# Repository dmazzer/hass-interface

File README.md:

# hass-interface
Hardware interface for Home Assistant

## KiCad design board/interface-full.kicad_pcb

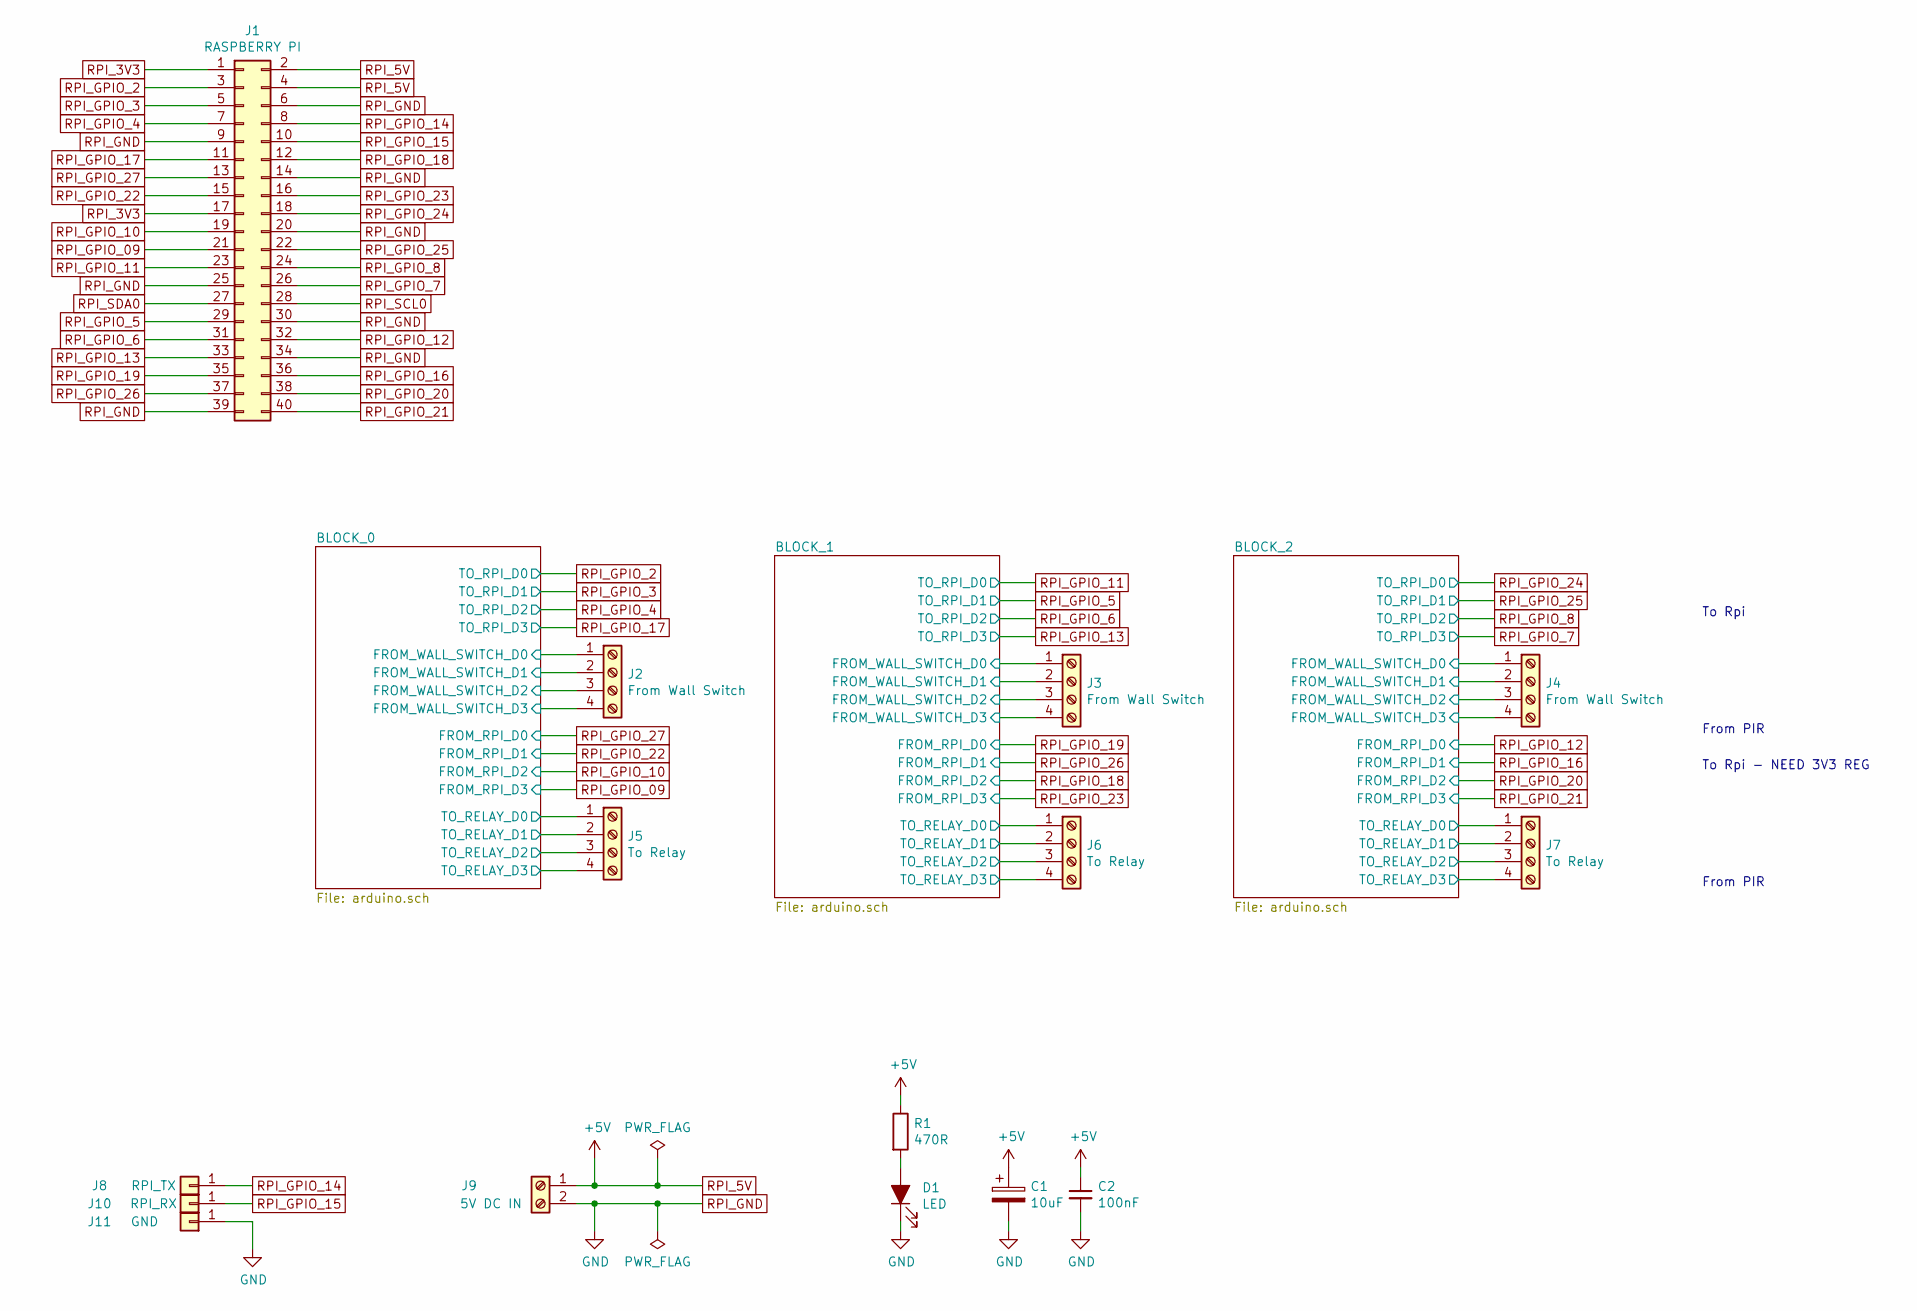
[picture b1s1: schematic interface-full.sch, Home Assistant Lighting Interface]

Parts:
C1: 10uF; CP_Radial_D5.0mm_P2.50mm
C2: 100nF; C_0805_2012Metric_Pad1.15x1.40mm_HandSolder
D1: LED; LED_1206_3216Metric_Pad1.42x1.75mm_HandSolder
J1: RASPBERRY PI; PinSocket_2x20_P2.54mm_Vertical
J2, J3, J4: From Wall Switch; TerminalBlock_Phoenix_MKDS-1,5-4-5.08_1x04_P5.08mm_Horizont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
J5, J6, J7: To Relay; TerminalBlock_Phoenix_MKDS-1,5-4-5.08_1x04_P5.08mm_Horizont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
J8: RPI_TX; PinHeader_1x01_P2.54mm_Vertical
J9: 5V DC IN; TerminalBlock_Phoenix_MKDS-1,5-2-5.08_1x02_P5.08mm_Horizont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
J10: RPI_RX; PinHeader_1x01_P2.54mm_Vertical
J11: GND; PinHeader_1x01_P2.54mm_Vertical
R1: 470R; R_0805_2012Metric_Pad1.15x1.40mm_HandSolder

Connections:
/BLOCK_0/FROM_WALL_SWITCH_D0: J2.1; also elsewhere on the board
/BLOCK_0/FROM_WALL_SWITCH_D1: J2.2; also elsewhere on the board
/BLOCK_0/FROM_WALL_SWITCH_D2: J2.3; also elsewhere on the board
/BLOCK_0/FROM_WALL_SWITCH_D3: J2.4; also elsewhere on the board
/BLOCK_0/TO_RELAY_D0: J5.1; also elsewhere on the board
/BLOCK_0/TO_RELAY_D1: J5.2; also elsewhere on the board
/BLOCK_0/TO_RELAY_D2: J5.3; also elsewhere on the board
/BLOCK_0/TO_RELAY_D3: J5.4; also elsewhere on the board
/BLOCK_1/FROM_WALL_SWITCH_D0: J3.1; also elsewhere on the board
/BLOCK_1/FROM_WALL_SWITCH_D1: J3.2; also elsewhere on the board
/BLOCK_1/FROM_WALL_SWITCH_D2: J3.3; also elsewhere on the board
/BLOCK_1/FROM_WALL_SWITCH_D3: J3.4; also elsewhere on the board
/BLOCK_1/TO_RELAY_D0: J6.1; also elsewhere on the board
/BLOCK_1/TO_RELAY_D1: J6.2; also elsewhere on the board
/BLOCK_1/TO_RELAY_D2: J6.3; also elsewhere on the board
/BLOCK_1/TO_RELAY_D3: J6.4; also elsewhere on the board
/BLOCK_2/FROM_WALL_SWITCH_D0: J4.1; also elsewhere on the board
/BLOCK_2/FROM_WALL_SWITCH_D1: J4.2; also elsewhere on the board
/BLOCK_2/FROM_WALL_SWITCH_D2: J4.3; also elsewhere on the board
/BLOCK_2/FROM_WALL_SWITCH_D3: J4.4; also elsewhere on the board
/BLOCK_2/TO_RELAY_D0: J7.1; also elsewhere on the board
/BLOCK_2/TO_RELAY_D1: J7.2; also elsewhere on the board
/BLOCK_2/TO_RELAY_D2: J7.3; also elsewhere on the board
/BLOCK_2/TO_RELAY_D3: J7.4; also elsewhere on the board
unnamed: D1.2 (A), R1.2
RPI_3V3: J1.1, J1.17
RPI_5V: C1.1, C2.1, J1.2, J1.4, J9.1, R1.1; also elsewhere on the board
RPI_GND: C1.2, C2.2, D1.1 (K), J1.6, J1.9, J1.14, J1.20, J1.25, J1.30, J1.34, J1.39, J9.2, J11.1; also elsewhere on the board
RPI_GPIO_2: J1.3; also elsewhere on the board
RPI_GPIO_3: J1.5; also elsewhere on the board
RPI_GPIO_4: J1.7; also elsewhere on the board
RPI_GPIO_5: J1.29; also elsewhere on the board
RPI_GPIO_6: J1.31; also elsewhere on the board
RPI_GPIO_7: J1.26; also elsewhere on the board
RPI_GPIO_8: J1.24; also elsewhere on the board
RPI_GPIO_09: J1.21; also elsewhere on the board
RPI_GPIO_10: J1.19; also elsewhere on the board
RPI_GPIO_11: J1.23; also elsewhere on the board
RPI_GPIO_12: J1.32; also elsewhere on the board
RPI_GPIO_13: J1.33; also elsewhere on the board
RPI_GPIO_14: J1.8, J8.1
RPI_GPIO_15: J1.10, J10.1
RPI_GPIO_16: J1.36; also elsewhere on the board
RPI_GPIO_17: J1.11; also elsewhere on the board
RPI_GPIO_18: J1.12; also elsewhere on the board
RPI_GPIO_19: J1.35; also elsewhere on the board
RPI_GPIO_20: J1.38; also elsewhere on the board
RPI_GPIO_21: J1.40; also elsewhere on the board
RPI_GPIO_22: J1.15; also elsewhere on the board
RPI_GPIO_23: J1.16; also elsewhere on the board
RPI_GPIO_24: J1.18; also elsewhere on the board
RPI_GPIO_25: J1.22; also elsewhere on the board
RPI_GPIO_26: J1.37; also elsewhere on the board
RPI_GPIO_27: J1.13; also elsewhere on the board
RPI_SCL0: J1.28
RPI_SDA0: J1.27

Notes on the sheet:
From PIR
To Rpi
To Rpi - NEED 3V3 REG

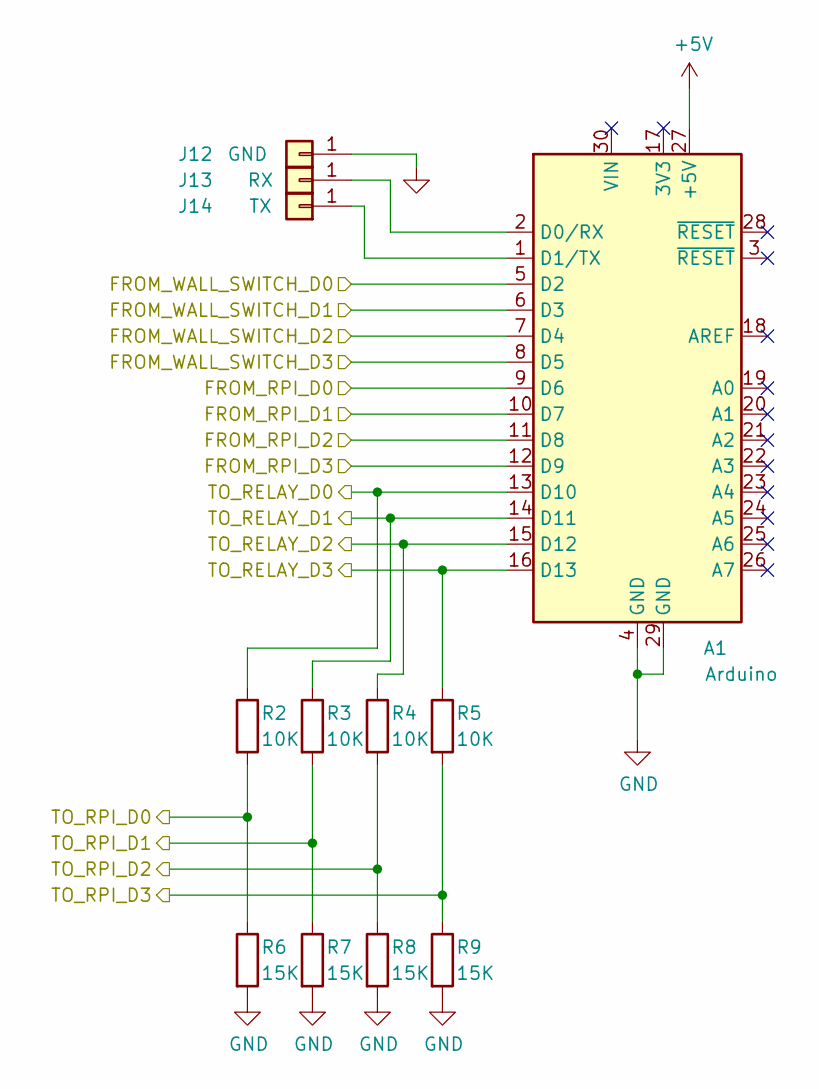
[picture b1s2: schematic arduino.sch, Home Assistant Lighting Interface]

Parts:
A1: Arduino; Arduino_Nano
J12: GND; PinHeader_1x01_P2.54mm_Vertical
J13: RX; PinHeader_1x01_P2.54mm_Vertical
J14: TX; PinHeader_1x01_P2.54mm_Vertical
R2, R3, R4, R5: 10K; R_0805_2012Metric_Pad1.15x1.40mm_HandSolder
R6, R7, R8, R9: 15K; R_0805_2012Metric_Pad1.15x1.40mm_HandSolder

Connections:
/BLOCK_0/FROM_WALL_SWITCH_D0: A1.5 (D2); also elsewhere on the board
/BLOCK_0/FROM_WALL_SWITCH_D1: A1.6 (D3); also elsewhere on the board
/BLOCK_0/FROM_WALL_SWITCH_D2: A1.7 (D4); also elsewhere on the board
/BLOCK_0/FROM_WALL_SWITCH_D3: A1.8 (D5); also elsewhere on the board
/BLOCK_0/TO_RELAY_D0: A1.13 (D10), R2.1; also elsewhere on the board
/BLOCK_0/TO_RELAY_D1: A1.14 (D11), R3.1; also elsewhere on the board
/BLOCK_0/TO_RELAY_D2: A1.15 (D12), R4.1; also elsewhere on the board
/BLOCK_0/TO_RELAY_D3: A1.16 (D13), R5.1; also elsewhere on the board
unnamed: A1.1 (D1/TX), J14.1
unnamed: A1.2 (D0/RX), J13.1
RPI_5V: A1.27 (+5V); also elsewhere on the board
RPI_GND: A1.4 (GND), A1.29 (GND), J12.1, R6.2, R7.2, R8.2, R9.2; also elsewhere on the board
RPI_GPIO_2: R2.2, R6.1; also elsewhere on the board
RPI_GPIO_3: R3.2, R7.1; also elsewhere on the board
RPI_GPIO_4: R4.2, R8.1; also elsewhere on the board
RPI_GPIO_09: A1.12 (D9); also elsewhere on the board
RPI_GPIO_10: A1.11 (D8); also elsewhere on the board
RPI_GPIO_17: R5.2, R9.1; also elsewhere on the board
RPI_GPIO_22: A1.10 (D7); also elsewhere on the board
RPI_GPIO_27: A1.9 (D6); also elsewhere on the board

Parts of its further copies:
A2, A3: Arduino; Arduino_Nano
J15, J18: GND; PinHeader_1x01_P2.54mm_Vertical
J16, J19: RX; PinHeader_1x01_P2.54mm_Vertical
J17, J20: TX; PinHeader_1x01_P2.54mm_Vertical
R11, R12, R13, R14, R20, R21, R22, R23: 10K; R_0805_2012Metric_Pad1.15x1.40mm_HandSolder
R15, R16, R17, R18, R24, R25, R26, R27: 15K; R_0805_2012Metric_Pad1.15x1.40mm_HandSolder

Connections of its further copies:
/BLOCK_1/FROM_WALL_SWITCH_D0: A2.5 (D2); also elsewhere on the board
/BLOCK_1/FROM_WALL_SWITCH_D1: A2.6 (D3); also elsewhere on the board
/BLOCK_1/FROM_WALL_SWITCH_D2: A2.7 (D4); also elsewhere on the board
/BLOCK_1/FROM_WALL_SWITCH_D3: A2.8 (D5); also elsewhere on the board
/BLOCK_1/TO_RELAY_D0: A2.13 (D10), R11.1; also elsewhere on the board
/BLOCK_1/TO_RELAY_D1: A2.14 (D11), R12.1; also elsewhere on the board
/BLOCK_1/TO_RELAY_D2: A2.15 (D12), R13.1; also elsewhere on the board
/BLOCK_1/TO_RELAY_D3: A2.16 (D13), R14.1; also elsewhere on the board
/BLOCK_2/FROM_WALL_SWITCH_D0: A3.5 (D2); also elsewhere on the board
/BLOCK_2/FROM_WALL_SWITCH_D1: A3.6 (D3); also elsewhere on the board
/BLOCK_2/FROM_WALL_SWITCH_D2: A3.7 (D4); also elsewhere on the board
/BLOCK_2/FROM_WALL_SWITCH_D3: A3.8 (D5); also elsewhere on the board
/BLOCK_2/TO_RELAY_D0: A3.13 (D10), R20.1; also elsewhere on the board
/BLOCK_2/TO_RELAY_D1: A3.14 (D11), R21.1; also elsewhere on the board
/BLOCK_2/TO_RELAY_D2: A3.15 (D12), R22.1; also elsewhere on the board
/BLOCK_2/TO_RELAY_D3: A3.16 (D13), R23.1; also elsewhere on the board
unnamed: A2.1 (D1/TX), J17.1
unnamed: A2.2 (D0/RX), J16.1
unnamed: A3.1 (D1/TX), J20.1
unnamed: A3.2 (D0/RX), J19.1
RPI_5V: A2.27 (+5V), A3.27 (+5V); also elsewhere on the board
RPI_GND: A2.4 (GND), A2.29 (GND), A3.4 (GND), A3.29 (GND), J15.1, J18.1, R15.2, R16.2, R17.2, R18.2, R24.2, R25.2, R26.2, R27.2; also elsewhere on the board
RPI_GPIO_5: R12.2, R16.1; also elsewhere on the board
RPI_GPIO_6: R13.2, R17.1; also elsewhere on the board
RPI_GPIO_7: R23.2, R27.1; also elsewhere on the board
RPI_GPIO_8: R22.2, R26.1; also elsewhere on the board
RPI_GPIO_11: R11.2, R15.1; also elsewhere on the board
RPI_GPIO_12: A3.9 (D6); also elsewhere on the board
RPI_GPIO_13: R14.2, R18.1; also elsewhere on the board
RPI_GPIO_16: A3.10 (D7); also elsewhere on the board
RPI_GPIO_18: A2.11 (D8); also elsewhere on the board
RPI_GPIO_19: A2.9 (D6); also elsewhere on the board
RPI_GPIO_20: A3.11 (D8); also elsewhere on the board
RPI_GPIO_21: A3.12 (D9); also elsewhere on the board
RPI_GPIO_23: A2.12 (D9); also elsewhere on the board
RPI_GPIO_24: R20.2, R24.1; also elsewhere on the board
RPI_GPIO_25: R21.2, R25.1; also elsewhere on the board
RPI_GPIO_26: A2.10 (D7); also elsewhere on the board

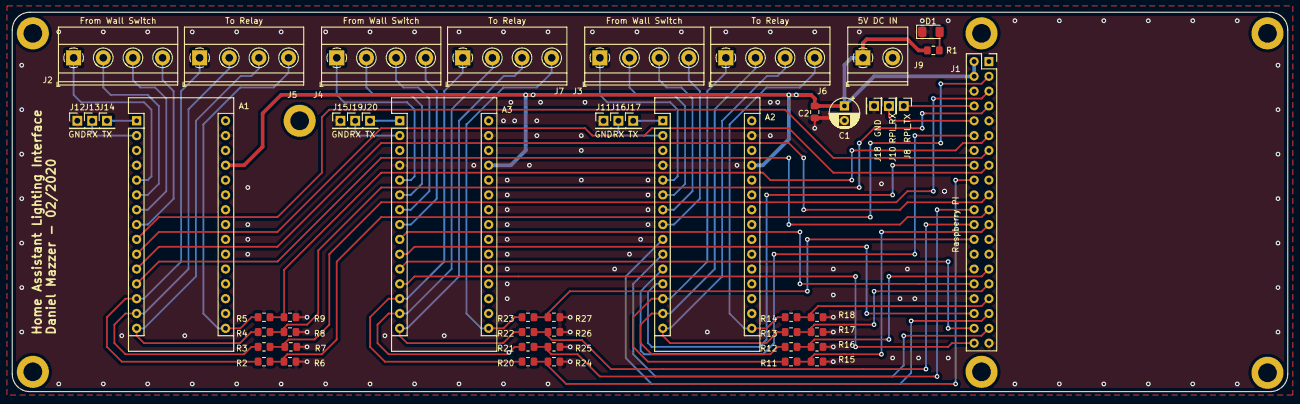
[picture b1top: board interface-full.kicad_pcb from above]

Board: 2 copper layers, 218.6 x 65.0 mm, 52 parts (0 on the bottom side), 60 nets.

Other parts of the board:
Raspberry PI: MountingHole_3.2mm_M3_ISO14580_Pad

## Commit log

2020-02-06 adding work in progress files
2020-02-09 board done
2020-02-09 moving hardware files to board subdir
2020-02-09 adding firmware files
2020-02-09 restoring removed file by mistake
2020-04-27 firmware changes to support toggle and momentary swithces. I have no idea what was the hardware modifications
2020-06-06 change sch to match rpi gpio numbering
2020-06-06 nothing
2020-07-30 Fix debug led blink
2020-07-30 Fix RPI GPIO numbers
